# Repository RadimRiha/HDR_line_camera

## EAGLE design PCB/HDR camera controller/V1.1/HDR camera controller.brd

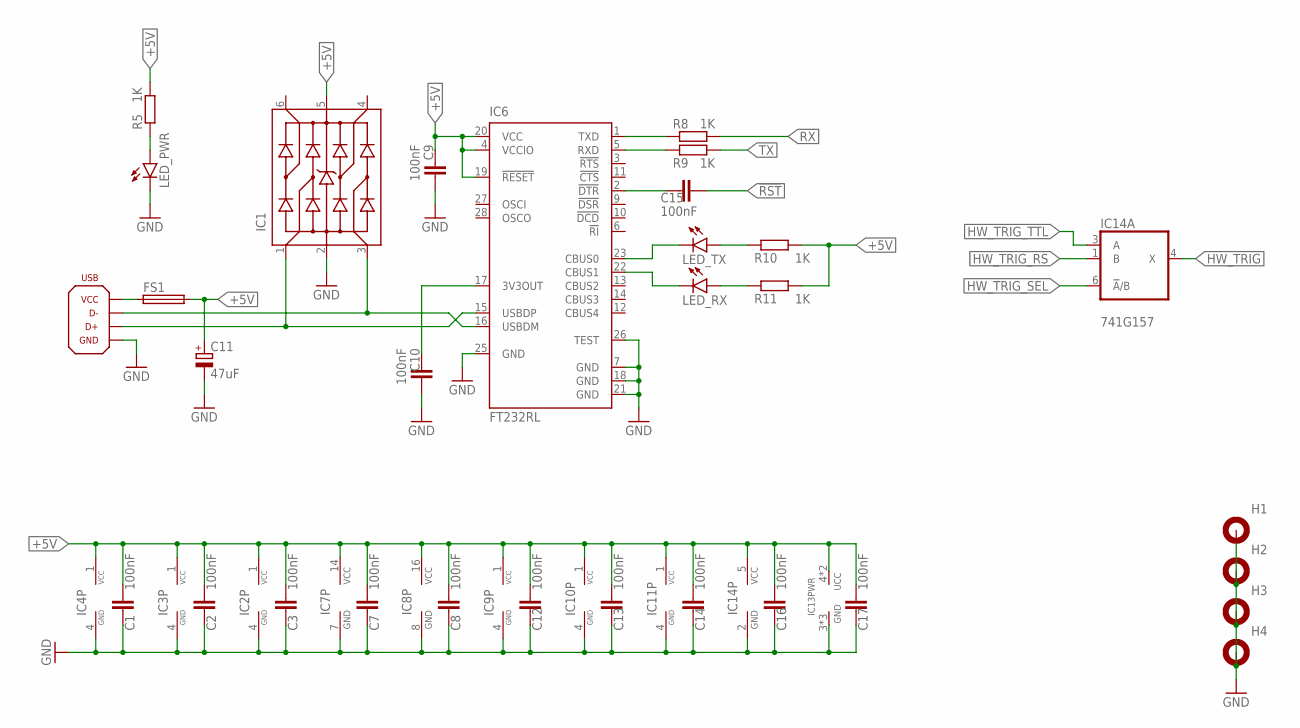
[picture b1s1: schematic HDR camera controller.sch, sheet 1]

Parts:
C1, C2, C3, C7, C8, C9, C10, C12, C13, C14, C15, C16, C17: 100nF; C0805
C11: 47uF; 153CLV-0605; MPN SC1E476M6L005VR
FS1: POLYFUSE_1210; 1210; MPN SM010-60
H1, H2, H3, H4: HOLE-3MM_PLATED; 3MM_PLATED
IC1: USBLC6-4; SOT23-6; MPN USBLC6
IC2, IC3, IC4, IC9, IC10, IC11: RS422-SO8; SO08; MPN DS8921AMX/NOPB
IC6: FT232RL; SSOP28
IC7: 74HC00D; SO14; MPN SN74HC00DR
IC8: 74HC139D; SO16; MPN SN74HC139DR
IC13: ATMEGA48/88/168/328-AU; TQFP32-08
IC14: 741G157; SOT457W_PHILIPS; MPN 74LVC1G157GV.125
LED_PWR: LEDSML0805; SML0805
LED_RX: LEDSML0805; SML0805
LED_TX: LEDSML0805; SML0805
R5, R8, R9, R10, R11: 1K; R0805
USB: USB_AB-B_SMD; USB_B_SMD; MPN USBB-G-SMD

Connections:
!RST: C15.1; also elsewhere on the board
+5V: C1.1, C2.1, C3.1, C7.1, C8.1, C9.2, C11.+, C12.1, C13.1, C14.1, C16.1, C17.1, FS1.2, IC1.5, IC2.1 (VCC), IC3.1 (VCC), IC4.1 (VCC), IC6.4 (VCCIO), IC6.19 (!RESET), IC6.20 (VCC), IC7.14 (VCC), IC8.16 (VCC), IC9.1 (VCC), IC10.1 (VCC), IC11.1 (VCC), IC13.4 (UCC), IC13.6 (UCC), IC14.5 (VCC), R5.2, R10.2, R11.2; also elsewhere on the board
GND: C1.2, C2.2, C3.2, C7.2, C8.2, C9.1, C10.1, C11.-, C12.2, C13.2, C14.2, C16.2, C17.2, H1.1, H2.1, H3.1, H4.1, IC1.2, IC2.4 (GND), IC3.4 (GND), IC4.4 (GND), IC6.7 (GND), IC6.18 (GND), IC6.21 (GND), IC6.25 (GND), IC6.26 (TEST), IC7.7 (GND), IC8.8 (GND), IC9.4 (GND), IC10.4 (GND), IC11.4 (GND), IC13.3 (GND), IC13.5 (GND), IC13.21 (GND), IC14.2 (GND), LED_PWR.C, USB.4 (GND), USB.G1 (GND), USB.G2 (GND); also elsewhere on the board
HW_TRIG: IC14.4 (X); also elsewhere on the board
HW_TRIG_RS: IC14.1 (B); also elsewhere on the board
HW_TRIG_SEL: IC14.6 (!A!/B); also elsewhere on the board
HW_TRIG_TTL: IC14.3 (A); also elsewhere on the board
unnamed: IC1.1, IC6.15 (USBDP), USB.3 (D+)
unnamed: IC1.3, IC6.16 (USBDM), USB.2 (D-)
unnamed: FS1.1, USB.1 (VCC)
unnamed: C10.2, IC6.17 (3V3OUT)
unnamed: IC6.1 (TXD), R8.1
unnamed: IC6.5 (RXD), R9.1
unnamed: C15.2, IC6.2 (!DTR)
unnamed: IC6.22 (CBUS1), LED_RX.C
unnamed: IC6.23 (CBUS0), LED_TX.C
unnamed: LED_TX.A, R10.1
unnamed: LED_RX.A, R11.1
unnamed: LED_PWR.A, R5.1
RX: R8.2; also elsewhere on the board
TX: R9.2; also elsewhere on the board

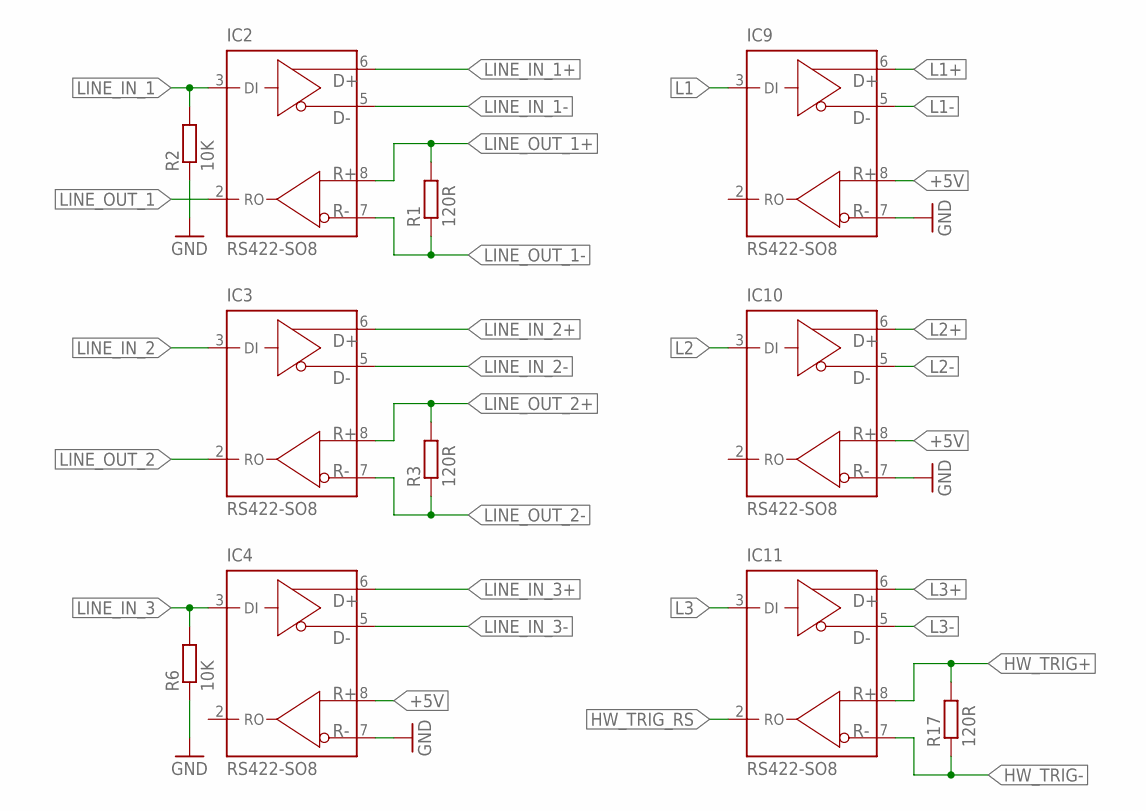
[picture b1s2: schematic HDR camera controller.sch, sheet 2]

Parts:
IC2, IC3, IC4, IC9, IC10, IC11: RS422-SO8; SO08; MPN DS8921AMX/NOPB
R1, R3, R17: 120R; R0805
R2, R6: 10K; R0805

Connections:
+5V: IC4.8 (R+), IC9.8 (R+), IC10.8 (R+); also elsewhere on the board
GND: IC4.7 (R-), IC9.7 (R-), IC10.7 (R-), R2.1, R6.1; also elsewhere on the board
HW_TRIG+: IC11.8 (R+), R17.2; also elsewhere on the board
HW_TRIG-: IC11.7 (R-), R17.1; also elsewhere on the board
HW_TRIG_RS: IC11.2 (RO); also elsewhere on the board
L1: IC9.3 (DI); also elsewhere on the board
L1+: IC9.6 (D+); also elsewhere on the board
L1-: IC9.5 (D-); also elsewhere on the board
L2: IC10.3 (DI); also elsewhere on the board
L2+: IC10.6 (D+); also elsewhere on the board
L2-: IC10.5 (D-); also elsewhere on the board
L3: IC11.3 (DI); also elsewhere on the board
L3+: IC11.6 (D+); also elsewhere on the board
L3-: IC11.5 (D-); also elsewhere on the board
LINE_IN_1: IC2.3 (DI), R2.2; also elsewhere on the board
LINE_IN_1+: IC2.6 (D+); also elsewhere on the board
LINE_IN_1-: IC2.5 (D-); also elsewhere on the board
LINE_IN_2: IC3.3 (DI); also elsewhere on the board
LINE_IN_2+: IC3.6 (D+); also elsewhere on the board
LINE_IN_2-: IC3.5 (D-); also elsewhere on the board
LINE_IN_3: IC4.3 (DI), R6.2
LINE_IN_3+: IC4.6 (D+); also elsewhere on the board
LINE_IN_3-: IC4.5 (D-); also elsewhere on the board
LINE_OUT_1: IC2.2 (RO); also elsewhere on the board
LINE_OUT_1+: IC2.8 (R+), R1.2; also elsewhere on the board
LINE_OUT_1-: IC2.7 (R-), R1.1; also elsewhere on the board
LINE_OUT_2: IC3.2 (RO); also elsewhere on the board
LINE_OUT_2+: IC3.8 (R+), R3.2; also elsewhere on the board
LINE_OUT_2-: IC3.7 (R-), R3.1; also elsewhere on the board

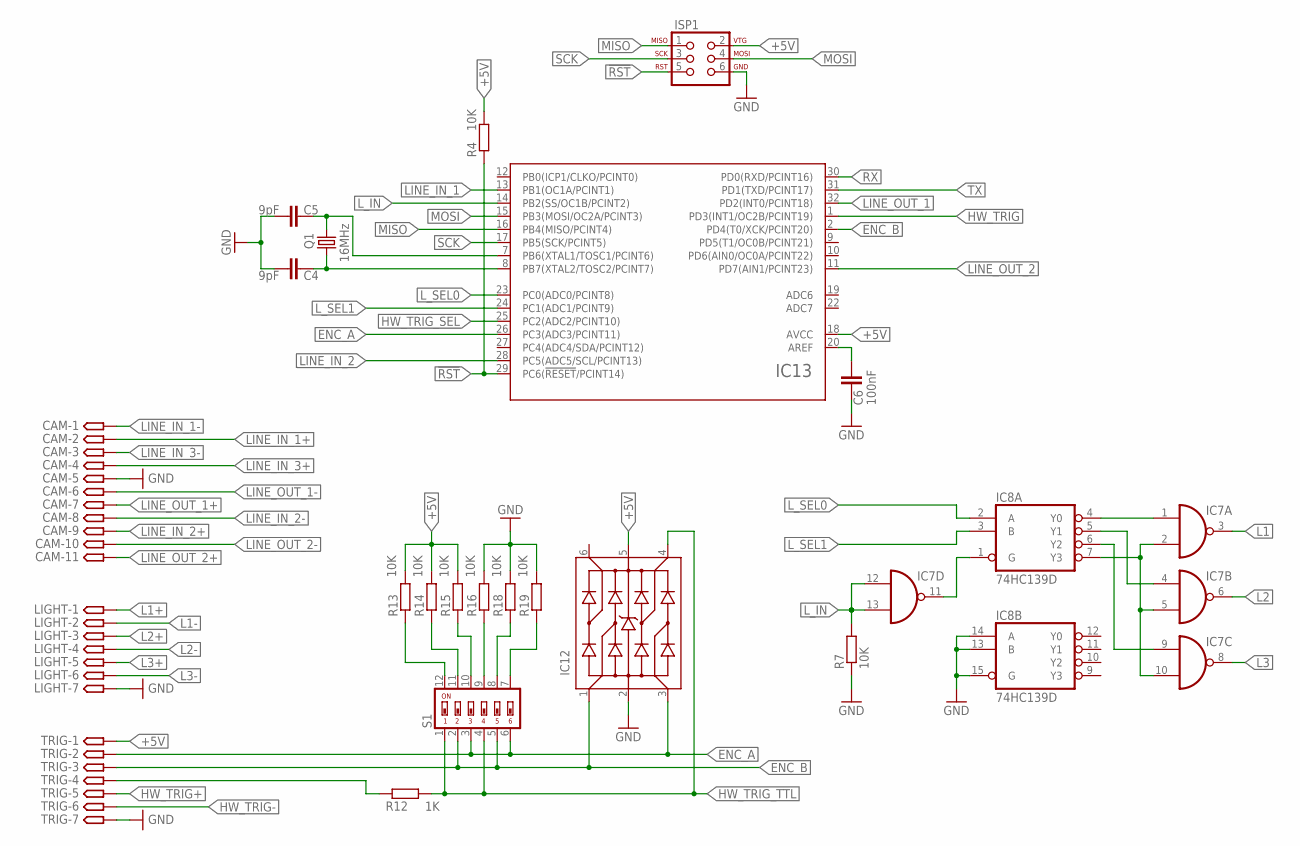
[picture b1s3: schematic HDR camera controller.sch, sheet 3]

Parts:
C4, C5: 9pF; C0805
C6: 100nF; C0805
CAM: SMPAD-11; S-11P
IC7: 74HC00D; SO14; MPN SN74HC00DR
IC8: 74HC139D; SO16; MPN SN74HC139DR
IC12: USBLC6-4; SOT23-6; MPN USBLC6
IC13: ATMEGA48/88/168/328-AU; TQFP32-08
ISP1: ISP-SMD; ISP_SMD
LIGHT: SMPAD-7; S-7P
Q1: 16MHz; CRYSTAL-3.2X2.5; MPN 3225-16M-SR
R4, R7, R13, R14, R15, R16, R18, R19: 10K; R0805
R12: 1K; R0805
S1: SWS006; SMS-006; MPN A6S-6102-H
TRIG: SMPAD-7; S-7P

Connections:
!RST: IC13.29 (PC6(!RESET!/PCINT14)), ISP1.5 (RST), R4.1; also elsewhere on the board
+5V: IC12.5, IC13.18 (AVCC), ISP1.2 (VTG), R4.2, R13.2, R14.2, R15.2, TRIG.1; also elsewhere on the board
ENC_A: IC12.3, IC13.26 (PC3(ADC3/PCINT11)), S1.3, S1.6, TRIG.2
ENC_B: IC12.1, IC13.2 (PD4(T0/XCK/PCINT20)), S1.2, S1.5, TRIG.3
GND: C4.1, C5.1, C6.2, CAM.5, IC8.13 (B), IC8.14 (A), IC8.15 (G), IC12.2, ISP1.6 (GND), LIGHT.7, R7.1, R16.2, R18.2, R19.2, TRIG.7; also elsewhere on the board
HW_TRIG: IC13.1 (PD3(INT1/OC2B/PCINT19)); also elsewhere on the board
HW_TRIG+: TRIG.5; also elsewhere on the board
HW_TRIG-: TRIG.6; also elsewhere on the board
HW_TRIG_SEL: IC13.25 (PC2(ADC2/PCINT10)); also elsewhere on the board
HW_TRIG_TTL: IC12.4, R12.2, S1.1, S1.4; also elsewhere on the board
L1: IC7.3 (O); also elsewhere on the board
L1+: LIGHT.1; also elsewhere on the board
L1-: LIGHT.2; also elsewhere on the board
L2: IC7.6 (O); also elsewhere on the board
L2+: LIGHT.3; also elsewhere on the board
L2-: LIGHT.4; also elsewhere on the board
L3: IC7.8 (O); also elsewhere on the board
L3+: LIGHT.5; also elsewhere on the board
L3-: LIGHT.6; also elsewhere on the board
LINE_IN_1: IC13.13 (PB1(OC1A/PCINT1)); also elsewhere on the board
LINE_IN_1+: CAM.2; also elsewhere on the board
LINE_IN_1-: CAM.1; also elsewhere on the board
LINE_IN_2: IC13.28 (PC5(ADC5/SCL/PCINT13)); also elsewhere on the board
LINE_IN_2+: CAM.9; also elsewhere on the board
LINE_IN_2-: CAM.8; also elsewhere on the board
LINE_IN_3+: CAM.4; also elsewhere on the board
LINE_IN_3-: CAM.3; also elsewhere on the board
LINE_OUT_1: IC13.32 (PD2(INT0/PCINT18)); also elsewhere on the board
LINE_OUT_1+: CAM.7; also elsewhere on the board
LINE_OUT_1-: CAM.6; also elsewhere on the board
LINE_OUT_2: IC13.11 (PD7(AIN1/PCINT23)); also elsewhere on the board
LINE_OUT_2+: CAM.11; also elsewhere on the board
LINE_OUT_2-: CAM.10; also elsewhere on the board
L_IN: IC7.12 (I0), IC7.13 (I1), IC13.14 (PB2(SS/OC1B/PCINT2)), R7.2
L_SEL0: IC8.2 (A), IC13.23 (PC0(ADC0/PCINT8))
L_SEL1: IC8.3 (B), IC13.24 (PC1(ADC1/PCINT9))
MISO: IC13.16 (PB4(MISO/PCINT4)), ISP1.1 (MISO)
MOSI: IC13.15 (PB3(MOSI/OC2A/PCINT3)), ISP1.4 (MOSI)
unnamed: C5.2, IC13.7 (PB6(XTAL1/TOSC1/PCINT6)), Q1.3 (2)
unnamed: C4.2, IC13.8 (PB7(XTAL2/TOSC2/PCINT7)), Q1.1
unnamed: IC7.11 (O), IC8.1 (G)
unnamed: IC7.1 (I0), IC8.4 (Y0)
unnamed: IC7.4 (I0), IC8.5 (Y1)
unnamed: IC7.9 (I0), IC8.6 (Y2)
unnamed: IC7.2 (I1), IC7.5 (I1), IC7.10 (I1), IC8.7 (Y3)
unnamed: R12.1, TRIG.4
unnamed: R16.1, S1.9
unnamed: R18.1, S1.8
unnamed: R19.1, S1.7
unnamed: R15.1, S1.10
unnamed: R14.1, S1.11
unnamed: R13.1, S1.12
unnamed: C6.1, IC13.20 (AREF)
RX: IC13.30 (PD0(RXD/PCINT16)); also elsewhere on the board
SCK: IC13.17 (PB5(SCK/PCINT5)), ISP1.3 (SCK)
TX: IC13.31 (PD1(TXD/PCINT17)); also elsewhere on the board

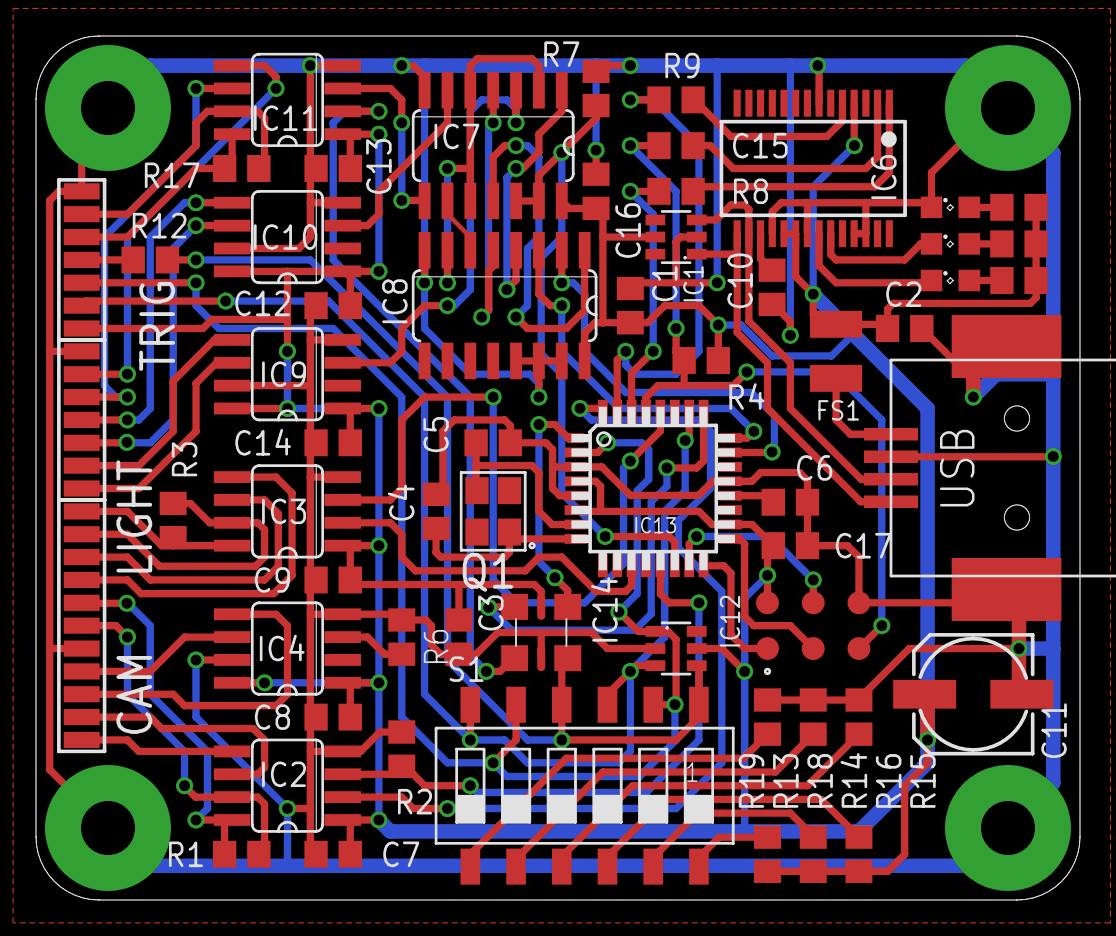
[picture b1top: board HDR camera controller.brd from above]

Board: 2 copper layers, 58.0 x 48.0 mm, 64 parts (0 on the bottom side), 70 nets.

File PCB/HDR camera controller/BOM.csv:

Part;Value;Device;Package;Description;MPN
C4;9pF;C-EUC0805;C0805;CAPACITOR, European symbol;
C5;9pF;C-EUC0805;C0805;CAPACITOR, European symbol;
C1;100nF;C-EUC0805;C0805;CAPACITOR, European symbol;
C2;100nF;C-EUC0805;C0805;CAPACITOR, European symbol;
C3;100nF;C-EUC0805;C0805;CAPACITOR, European symbol;
C6;100nF;C-EUC0805;C0805;CAPACITOR, European symbol;
C7;100nF;C-EUC0805;C0805;CAPACITOR, European symbol;
C8;100nF;C-EUC0805;C0805;CAPACITOR, European symbol;
C9;100nF;C-EUC0805;C0805;CAPACITOR, European symbol;
C10;100nF;C-EUC0805;C0805;CAPACITOR, European symbol;
C12;100nF;C-EUC0805;C0805;CAPACITOR, European symbol;
C13;100nF;C-EUC0805;C0805;CAPACITOR, European symbol;
C14;100nF;C-EUC0805;C0805;CAPACITOR, European symbol;
C15;100nF;C-EUC0805;C0805;CAPACITOR, European symbol;
C16;100nF;C-EUC0805;C0805;CAPACITOR, European symbol;
C17;100nF;C-EUC0805;C0805;CAPACITOR, European symbol;
C11;47uF;CPOL-EU153CLV-0605;153CLV-0605;POLARIZED CAPACITOR, European symbol;SC1E476M6L005VR
R1;120R;R-EU_R0805;R0805;RESISTOR, European symbol;
R3;120R;R-EU_R0805;R0805;RESISTOR, European symbol;
R17;120R;R-EU_R0805;R0805;RESISTOR, European symbol;
R5;1K;R-EU_R0805;R0805;RESISTOR, European symbol;
R8;1K;R-EU_R0805;R0805;RESISTOR, European symbol;
R9;1K;R-EU_R0805;R0805;RESISTOR, European symbol;
R10;1K;R-EU_R0805;R0805;RESISTOR, European symbol;
R11;1K;R-EU_R0805;R0805;RESISTOR, European symbol;
R12;1K;R-EU_R0805;R0805;RESISTOR, European symbol;
R2;10K;R-EU_R0805;R0805;RESISTOR, European symbol;
R4;10K;R-EU_R0805;R0805;RESISTOR, European symbol;
R7;10K;R-EU_R0805;R0805;RESISTOR, European symbol;
R13;10K;R-EU_R0805;R0805;RESISTOR, European symbol;
R14;10K;R-EU_R0805;R0805;RESISTOR, European symbol;
R15;10K;R-EU_R0805;R0805;RESISTOR, European symbol;
R16;10K;R-EU_R0805;R0805;RESISTOR, European symbol;
R18;10K;R-EU_R0805;R0805;RESISTOR, European symbol;
R19;10K;R-EU_R0805;R0805;RESISTOR, European symbol;
IC6;FT232RL;FT232RL;SSOP28;;FT232RL
IC7;74HC00D;74HC00D;SO14;Quad 2-input NAND gate;SN74HC00DR
IC8;74HC139D;74HC139D;SO16;Dual 2-line to 4-line DECODER/DEMULTIPLEXER;SN74HC139DR
FS1;;POLYFUSE_1210;1210;;SM010-60
IC12;USBLC6-4;USBLC6-4;SOT23-6;SHOTTKY DIODE;USBLC6
IC1;USBLC6-4;USBLC6-4;SOT23-6;SHOTTKY DIODE;USBLC6
IC2;RS422-SO8;RS422-SO8;SO08;RS485 TRANSEIVER;DS8921AMX/NOPB
IC3;RS422-SO8;RS422-SO8;SO08;RS485 TRANSEIVER;DS8921AMX/NOPB
IC4;RS422-SO8;RS422-SO8;SO08;RS485 TRANSEIVER;DS8921AMX/NOPB
IC9;RS422-SO8;RS422-SO8;SO08;RS485 TRANSEIVER;DS8921AMX/NOPB
IC10;RS422-SO8;RS422-SO8;SO08;RS485 TRANSEIVER;DS8921AMX/NOPB
IC11;RS422-SO8;RS422-SO8;SO08;RS485 TRANSEIVER;DS8921AMX/NOPB
IC13;;ATMEGA48/88/168/328-AU;TQFP32-08;;
IC14;741G157;741G157;SOT457W_PHILIPS;;74LVC1G157GV.125
LED_PWR;;LEDSML0805;SML0805;LED;
LED_RX;;LEDSML0805;SML0805;LED;
LED_TX;;LEDSML0805;SML0805;LED;
Q1;16MHz;RESONATOR_CRY;CRYSTAL-3.2X2.5;;3225-16M-SR
S1;SWS006;SWS006;SMS-006;SMD Dip Switch 6 pol.;A6S-6102-H
USB;USB_AB-B_SMD;USB_AB-B_SMD;USB_B_SMD;;USBB-G-SMD

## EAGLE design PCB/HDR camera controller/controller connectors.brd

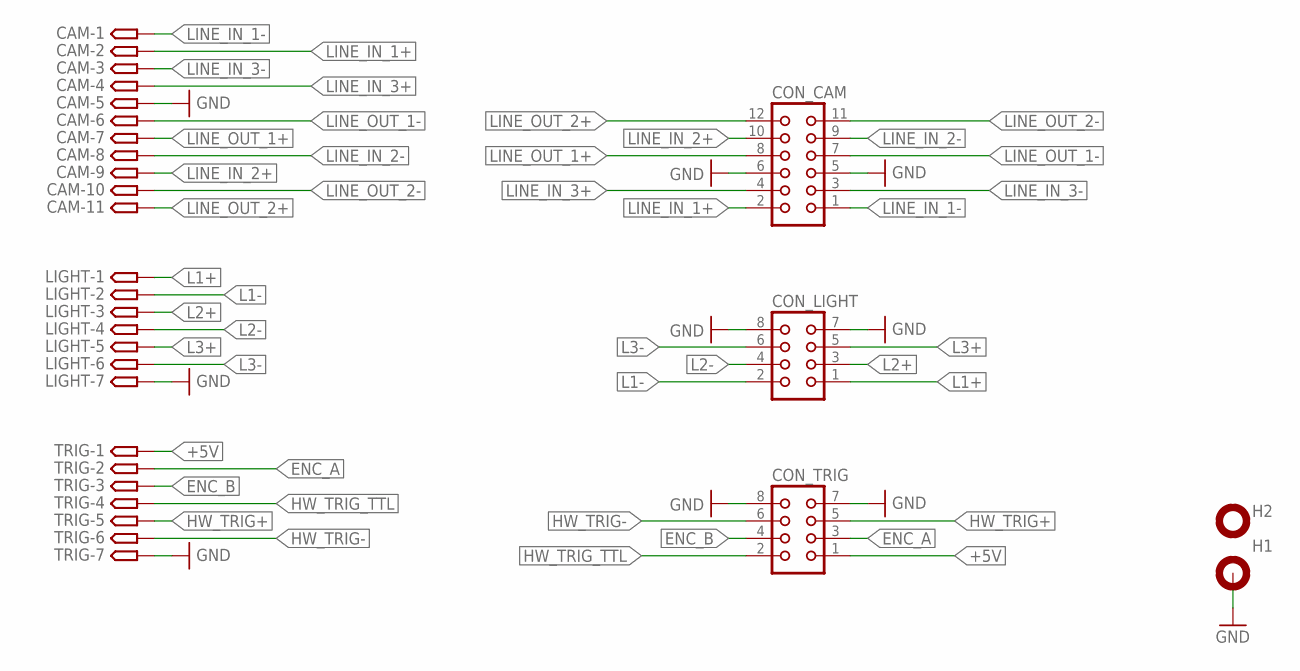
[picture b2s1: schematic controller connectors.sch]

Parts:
CAM: SMPAD-11; S-11P
CON_CAM: CON12; CON12_2MM
CON_LIGHT: CON8; CON8_2MM
CON_TRIG: CON8; CON8_2MM
H1: HOLE-3MM_PLATED; 3MM_PLATED
H2: HOLE_UNPLATED; 3MM_UNPLATED_1SIDE
LIGHT: SMPAD-7; S-7P
TRIG: SMPAD-7; S-7P

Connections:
+5V: CON_TRIG.1, TRIG.1
ENC_A: CON_TRIG.3, TRIG.2
ENC_B: CON_TRIG.4, TRIG.3
GND: CAM.5, CON_CAM.5, CON_CAM.6, CON_LIGHT.7, CON_LIGHT.8, CON_TRIG.7, CON_TRIG.8, H1.1, LIGHT.7, TRIG.7
HW_TRIG+: CON_TRIG.5, TRIG.5
HW_TRIG-: CON_TRIG.6, TRIG.6
HW_TRIG_TTL: CON_TRIG.2, TRIG.4
L1+: CON_LIGHT.1, LIGHT.1
L1-: CON_LIGHT.2, LIGHT.2
L2+: CON_LIGHT.3, LIGHT.3
L2-: CON_LIGHT.4, LIGHT.4
L3+: CON_LIGHT.5, LIGHT.5
L3-: CON_LIGHT.6, LIGHT.6
LINE_IN_1+: CAM.2, CON_CAM.2
LINE_IN_1-: CAM.1, CON_CAM.1
LINE_IN_2+: CAM.9, CON_CAM.10
LINE_IN_2-: CAM.8, CON_CAM.9
LINE_IN_3+: CAM.4, CON_CAM.4
LINE_IN_3-: CAM.3, CON_CAM.3
LINE_OUT_1+: CAM.7, CON_CAM.8
LINE_OUT_1-: CAM.6, CON_CAM.7
LINE_OUT_2+: CAM.11, CON_CAM.12
LINE_OUT_2-: CAM.10, CON_CAM.11

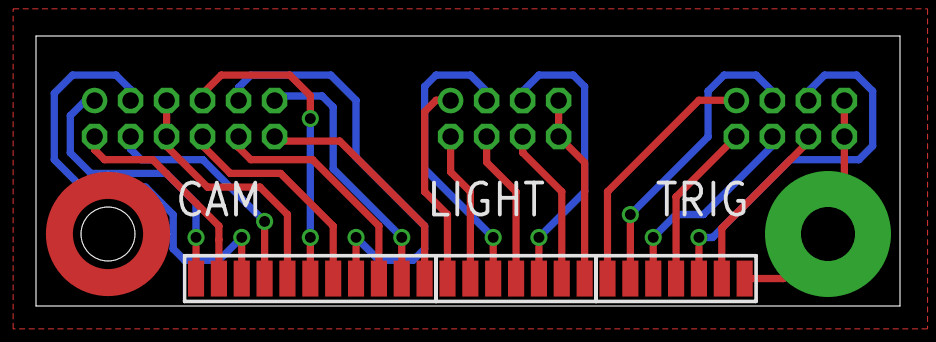
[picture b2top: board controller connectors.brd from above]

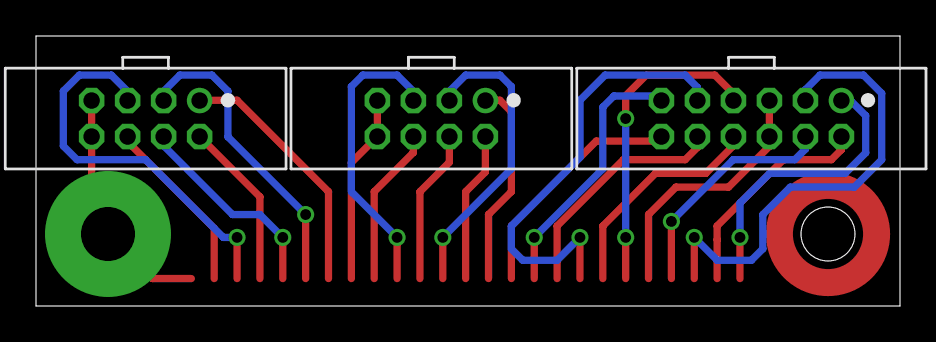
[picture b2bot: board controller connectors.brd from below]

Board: 2 copper layers, 48.0 x 15.0 mm, 8 parts (3 on the bottom side), 23 nets.

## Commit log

2021-09-24 PCB init
2021-09-28 MCU upload setup
2021-10-01 schematic update
    +USB
    +MCU
2021-10-23 trigger controller SW start
2021-10-24 Camera trigger wait interrupt
2021-10-24 develop
2021-10-24 trigger jitter fix
2021-10-24 controller USART communication
2021-10-25 controller basic string handling
2021-10-25 controller serial parameters get
2021-10-25 controller serial parameters set
2021-10-25 controller project restructuring
2021-10-25 controller serial parameters finished
2021-10-28 finished schematic
2021-10-28 PCB WIP
2021-10-30 PCB V1 manufacture
2021-11-06 Timed trigger WIP
2021-11-14 settings restructure WIP
2021-11-14 settings restructure bugfix
2021-11-14 minor bugfixes
2021-11-20 port to ATmega 328PB
2021-11-26 tweaks
2021-11-30 Lx output demux
2021-12-04 connector board
2021-12-21 amogus did not print, got rid of it :(
2021-12-30 EEPROM implemented and tested, PCB docs
2021-12-30 trigger setting tweak
2022-01-02 timing bugfix
2022-01-02 matlab scripts
2022-02-23 camera app switched to winforms
2022-02-24 settings
2022-02-28 switched to C#
2022-03-01 Sliders working
2022-03-01 more UI design
2022-03-03 Controller UI wip
2022-03-03 UI bugfixes
2022-03-05 Controller configuration wip
2022-03-06 Various UI bugfixes
2022-03-06 Untested controller config
2022-03-09 Partial PUO and PUP upload
2022-03-09 Slight restructure
2022-03-10 Non working camera disconnect event
2022-03-14 Frame width setting handling improved
2022-03-16 Image splitting
2022-03-16 Image counting added
2022-03-16 App exit event fixed
2022-03-17 Trigger startup bugfix
2022-03-23 Response function generator script
2022-03-23 Hdr processing WIP
2022-03-24 Hdr processing basic implementation
2022-04-06 Separating images into channels
2022-04-06 RGB image mixing
2022-04-06 Timed trigger startup bugfix
2022-04-06 Storing images as a special data type
2022-04-25 Optimization
2022-04-25 Image display options
2022-04-27 Bugfixes
2022-04-28 Window rename
2022-05-22 exception fix
2024-02-17 Timer1 changed to Timer3
2024-02-17 timed trigger fix
2024-02-18 Pulse stability improved
2024-02-18 code cleanup
2024-02-18 Pulse timer moved from TC0 to TC1
2024-02-23 Timing improvements
2024-02-23 Encoder with back counting implementation
2024-03-02 Line in 2 activation during 1st exposure
2024-04-04 Documentation
